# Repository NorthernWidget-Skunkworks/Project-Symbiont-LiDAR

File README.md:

# Project-Symbiont-LiDAR
Design files for a support and interface unit for the Garmin LiDAR Lite

***The symbiont.*** *Lichens, like this Reindeer Lichen found in northeastern
Minnesota, are a symbiosis between fungi and algae. Our symbiosis is between
silicon, copper, aluminum, and laser. But be it nature or machine, some
partnerships are truly mutual in their benefits. Photo by Homer Edward Price.*

The [LiDAR Lite](https://buy.garmin.com/en-US/US/p/578152/pn/010-01722-10) is a rangefinder from Garmin capable of returning distances to objects up to 40 m away. It is an effective sensor for water, snow, and ice levels, among other purposes. Extensive work to characterize the LiDAR Lite for environmental sensing of water levels has been performed by:

Paul, J. D., Buytaert, W., & Sah, N.(2020). A technical evaluation of lidar-based measurement of riverwater levels. *Water Resources Research*, *56*, e2019WR026810. https://doi.org/10.1029/2019WR026810

## Technical specifications

### Electronic Hardware

* Microcontroller (computer) core
  * ATTiny1634
  * [Firmware](Firmware) written in Arduino-compatible C++
  * 12 MHz
* Sensors
  * Externally connected: [Garmin LiDAR Lite v3 HP](https://buy.garmin.com/en-US/US/p/578152/pn/010-01722-10)
  * On board
    * MEMS accelerometer to detect board angle
    * Hall-effect sensor to for user to trigger with a magnet after providing a known angle to the accelerometer. This corrects for offset errors in the accelerometer, significantly improving its angular accuracy.
* Connections and communications protocols
  * [LiDAR Lite v3 HP](https://buy.garmin.com/en-US/US/p/578152/pn/010-01722-10)
    * 6-pin screw-terminal header
    * Switchable 5V power supply
    * I2C
  * Data logger
    * Power in and Ground
    * Digital communications
      * I2C
* Power
  * Voltage limits: 3.3 ~ 5.5V
  * Power consumption: ~0.5mA @ 4.5V, take reading every 60 seconds, then power down
  * Power conditioning: Provides an onboard, high power, step up to 5V to allow for interface to 3.3V loggers
* Fault recovery: Using intermediate system to emulate an I2C connection prevents a global lockup of the logger system
* Status LED
* Open-source licensing via CC BY-SA 4.0

### Electronic Software and Firmware

* Programmable using the Arduino IDE https://www.arduino.cc/en/main/software
* [Firmware](Firmware) available in this repository. At the time of writing, "LiDAR_InterfaceDemo" is the most up-to-date prototype firmware.
* [Software ](https://github.com/NorthernWidget-Skunkworks/Symbiont-LiDAR_Library) to use the Symbiont-LiDAR with Arduino-compatible devices
* Open-source licensing via GNU GPL 3.0

## Assembly

Assembling this sensor is possible by hand with sufficient skill and the following tools:
* Temperature-controlled soldering iron
* Hot-air rework station
* Equipment for stenciling with solder paste
* ESD-safe tweezers and workstation
* Solder wick

Most of the components on this board are coarse enough in pitch that assembly by hand is expected to be relatively straightforward. However, if you are concerned about this, there are PCB assembly workshops located in many parts of the world.
>> THOUGHT: I have basic instructions for assembly on the [Project Walrus](https://github.com/NorthernWidget-Skunkworks/Project-TPDH-Walrus) README; I will not reproduce these here just yet, as we might want to set up a separate assembly guide, mostly with good links to existing resources, since our writing something of this nature would be to reinvent the wheel.

## Firmware

### Downloading and installing the Arduino IDE

Go to https://www.arduino.cc/en/main/software. Choose the proper IDE version for your computer. For Windows, we suggest the non-app version to have more control over Arduino; this might change in the future. You will have to add custom libraries, so the web version will not work (at least, as of the time of writing). Download and install the Arduino IDE. Open it to begin the next steps.

### AVR ISP

To install firmware on the Symbiont board, you use the [2x3-pin 6-pin ICSP (also called ISP) header](https://www.digikey.com/product-detail/en/3m/929665-09-03-I/3M156313-06-ND/681796) with a special device called an "in-circuit system programmer" (or just "in-system programmer; yup, that's what the acronym stands for).

Many devices exist to upload firmware, including:
* The official [AVR ISP mkII](http://ww1.microchip.com/downloads/en/DeviceDoc/Atmel-42093-AVR-ISP-mkII_UserGuide.pdf) (no longer produced but available used)
* Using an [Arduino as an ISP](https://www.arduino.cc/en/tutorial/arduinoISP)
* The versatile [Olimex AVR-ISP-MK2](https://www.olimex.com/Products/AVR/Programmers/AVR-ISP-MK2/open-source-hardware)
* The [Adafruit USBtinyISP](https://www.adafruit.com/product/46)

### Uploading the firmware

Using this ISP, upload (as of the time of writing): [the Arduino sketch in this folder](Firmware/AdditionalFirmware/LiDAR_Accelerometer_InterfaceDemo). To do so, follow these steps:

1. Open the Arduino IDE.
2. Follow [these instructions](https://github.com/SpenceKonde/ATTinyCore/blob/master/Installation.md) to install the [ATTinyCore board definitions](https://github.com/SpenceKonde/ATTinyCore)
3. Select [ATTiny1634](https://github.com/SpenceKonde/ATTinyCore/blob/master/avr/extras/ATtiny_1634.md) **(No bootloader)**
4. Plug your ISP of choice into your computer (via a USB cable) and onto the 6-pin header. There are two ways to place it on; the header is aligned such that the ribbon cable should be facing away from the board while programming. If this fails without being able to upload, try flipping the header around. This should both power the board and provide communications.
5. Go to Tools --> Programmer and select the appropriate programmer based on what you are using.
6. Go to Tools --> Burn Bootloader. Yes, we know that you just selected "ATTiny1634 (No bootloader)", but this step sets the fuses, which configure their internal oscillator and brown-out detection.
7. Go to Sketch --> Upload Using Programmer. After several seconds, you learn whether you succeeded or failed. Hopefully it worked!

***Uploading using the in-system programmer.***

***Important note for Linux users:*** You must supply permissions to the Arduino IDE for it to be able to use the ICSP, or you will have to run it using `sudo`. The former option is better; the latter is easier in the moment.

***Note: Be sure to download and/or update drivers for your ISP.***

## Writing a program to connect to the Symbiont-LiDAR

Once it is bootloaded and connected with a LiDAR Lite sensor, you should be able to use any standard Arduino device to connect to it and read its data.

### Very simple Arduino code

This code is intended for any generic Arduino system.

```c++
// Include the Symbiont library
#include "SymbiontLiDAR.h"

// Declare variables -- just as strings
String header;
String data;

// Instantiate class
SymbiontLiDAR myLaser;

void setup(){
    // Begin Serial connection to computer at 38400 baud
    Serial.begin(38400);
    // Obtain the header just once
    header = myLaser.getHeader();
    // Print the header to the serial monitor
    Serial.println(header);
}

void loop(){
    // Take one reading every (10 + time to take reading) seconds
    // and print it to the screen
    myLaser.updateMeasurements();
    data = myLaser.getString();
    Serial.println(data);
    delay(10000); // Wait 10 seconds before the next reading, inefficiently
}
```

### Northern Widget Margay code

The [Margay data logger](github.com/NorthernWidget-Skunkworks/Project-Margay) is the lightweight and low-power open-source data-logging option from Northern Widget. It saves data to a local SD card and includes on-board status measurements and a low-drift real-time clock. We have written [a library to interface with the Margay](github.com/NorthernWidget-Skunkworks/Margay_Library), which can in turn be used to link the Margay with sensors.

```c++
// Include the Symbiont library
#include "Margay.h"
#include "SymbiontLiDAR.h"

// Declare variables -- just as strings
// Empty header to start; will include sensor labels and information
String header = "";
String data;

// Instantiate classes
SymbiontLiDAR myLaser;
Margay Logger; // Margay v2.2; UPDATE CODE TO INDICATE THIS

// I2CVals for Symbiont
uint8_t I2CVals[] = {0x50}; // DEFAULT

//Number of seconds between readings
uint32_t updateRate = 60;

void setup(){
    header = header + myLaser.getHeader();
    Logger.begin(I2CVals, sizeof(I2CVals), header);
    initialize();
}

void loop(){
    Logger.run(update, updateRate);
}

String update() {
    initialize();
    return myLaser.getString();
}

void initialize(){
    myLaser.begin();
}
```

### Northern Widget Resnik code

>> Currently nearly identical to Margay code, by design. Add telemetry with Particle Boron.

```c++
// Include the Symbiont library
#include "Resnik.h"
#include "SymbiontLiDAR.h"

// Declare variables -- just as strings
// Empty header to start; will include sensor labels and information
String header;
String data;

// Instantiate classes
SymbiontLiDAR myLaser;
Resnik Logger;

// I2CVals for Symbiont
uint8_t I2CVals[] = {0x50}; // DEFAULT

//Number of seconds between readings
uint32_t updateRate = 60;

void setup(){
    header = header + myLaser.getHeader();
    Logger.begin(I2CVals, sizeof(I2CVals), header);
    initialize();
}

void loop(){
    Logger.run(update, updateRate);
}

String update() {
    initialize();
    return myLaser.getString();
}

void initialize(){
    myLaser.begin();
}
```

## Housing and cabling

### Parts required

This is what we used for our build; you can be creative based on materials and availability.

* Main enclosure
  * Polycase box [WC-20F (clear lid)](https://www.polycase.com/wc-20f)
  * [2x \#4 screws](https://www.polycase.com/screws-mbr-100) to mount Symbiont in box
  * Cable gland ([Heyco M4365](https://www.heyco.com/Liquid_Tight_Cordgrips/product.cfm?product=Liquid-Tight-Cordgrips-Metric&section=Liquid_Tight_Cordgrips)) for cable to LiDAR Lite
  * Strain-relieved cable gland ([Heyco M4425](https://www.heyco.com/Liquid_Tight_Cordgrips/product.cfm?product=Liquid-Tight-Cordgrips-Pigtail-Metric&section=Liquid_Tight_Cordgrips)) for cable to logger
  * Desiccant packs
* LiDAR Rangefinder and attachment to enclosure
  * [LiDAR Lite sensor](https://www.sparkfun.com/products/14599)
  * [4 sealing screws](https://www.mcmaster.com/90825A144/): \#4-40 x 3/8"
  * [4 washers](https://www.mcmaster.com/90107A005) for \#4 screws
  * [4 cap nuts](https://www.mcmaster.com/99022A101) for \#4-40 screws
* Mounting plate
  * Material: Acetal (Delrin) sheet: 1/4" thick. We commmonly use [12x24" black](https://www.eplastics.com/ACTLBLK0-25012X24); the black pigment increases its UV resistance
  * Rectangular dimensions for mount: 127 x 95.25 x 6.35 mm (5.00" x 3.75" x 0.25")
  * [Design](https://easel.inventables.com/projects/VMmCoOyJyiiKTospk1NBBQ) on Easel for X-carve (see also [CNC files here](CNC)). Note the 7 mm depth to ensure that the bit cuts all the way through the Acetal; use a piece of scrap material on your cutting bed if you want to protect it.
* Mounting plate fasteners
  * 1/4"-20 hardware to attach the box to the mounting plate
    * Bolts: [1" long; hex head convenient; zinc-plated medium-grade (Grade 5) recommended for lower price with good corrosion resistance](https://www.mcmaster.com/92865A542)
    * Nuts: [Zinc-plated Grade 5](https://www.mcmaster.com/95462A029)
    * Washers: Zinc-plated [SAE](https://www.mcmaster.com/90126A029) or [USS](https://www.mcmaster.com/90108A413)
    * Lock washers: We typically use [split-lock washers](https://www.mcmaster.com/zinc-plated-steel-washers/), but [tooth-lock washers](https://www.mcmaster.com/91113A029) are good for high-vibration environments.
  * 2 U bolts: 1/4"-20, inner diameter 3/4" to 1 3/4", to attach the mounting plate to a pipe. We typically mount this sensor on 3/4" pipe or conduit, and recommend a U bolt designed to fit this ([1/4"-20, 1 1/8" inner diameter](https://www.mcmaster.com/u-bolts/u-bolts-with-mounting-plates/for-pipe-size~3-4/)). Weather/corrosion resistance is helpful, especially if you are concerned about later removing the U bolts.
* Cable to logger
  * 3 m (or less) [4-conductor AlphaWire](https://www.digikey.com/product-detail/en/alpha-wire/5004C-SL001/5004CSL001-ND/484976), stripped and tinned at both ends. Other cables will work too; this is what we have found to be highest quality and reliability. We cannot guarantee successful I<sup>2</sup>C communications over cables longer than 3 meters.

***Mounting plate perspective view in [Easel](https://easel.inventables.com/projects/VMmCoOyJyiiKTospk1NBBQ)*** *for easy integration with the X-carve series of lower cost CNC routers.*

### Assembly

Prior to assembly, ensure that you have:
* [Uploaded the firmware to the Symbiont board](#Uploading-the-firmware)
* Fabricated [the mounting plate](CNC) (see also the [Easel online CNC setup](https://easel.inventables.com/projects/VMmCoOyJyiiKTospk1NBBQ)) if desired.

1. Drill and tap 12 mm holes in the side of the box. Use a M12-1.5 tap for the threads.

2. Install the Symbiont board as shown below using two of the \#4 self-tapping screws.

3. Using the sealing screws, cap nuts, and washers, install the LiDAR Lite sensor onto the lid. By mounting the LiDAR Lite at an angle, you can fix it to the box lid in a way that still allows the box to open and close properly. The cap nuts go on the outside of the housing.

4. Thread the cables through the cable glands and attach them to the screw terminals. A 1.8 mm flat-head screwdriver can be very useful for this. Note that these cables cross the board in the above image (upper left) -- and that (unlike in the image!) you should do this *after* the board is in the box.

5. Using the switch in the box, select the desired communications protocol. For most of our uses, this is I2C.

6. Attach the cable to the data logger.

7. Test the LiDAR Lite unit.

8. When satisfied with the tests, turn off the data logger and place a protective cover over the lenses of the LiDAR Lite for safety during transport. We have [a set of "safety glasses" available for 3D printing](3Dprint). You may want to secure these in place with electrical tape.

9. Place desiccant in the box. I typically install two small desiccant packs on the side of the board above the switch and large capacitor and pack them in so they are unlikely to move; this is in order to keep the indicator LED visible.

10. Securely screw the lid onto the box to seal the LiDAR Lite + Symbiont unit.

11. Mark the corner of the box next to the Hall-effect sensor, and mark the orientations of the roll and pitch axes. The pitch axis should be positive when the long strain-relieved cable gland tilts upwards. The roll axis should be positive when, when looking at the side of the assembly such that the long strain-relieved cable gland is on the left and the laser rangefinder is pointed up, the laser rangefinder rolls towards you.

>> Add an annotated picture of Hall-Effect sensor location

12. Place the box on a measured flat surface and tap the magnet to the marked location by the Hall Effect sensor. This will appropriately zero the offsets for the sensor and increase its near-horizontal accuracy significantly. This must be done when the sensor is powered; the LED will light up during the full duration of magnetic contact. When connected to a logger, this can be done by putting the magnet in place, hitting the "RESET" button (e.g., on a Margay logger), and then holding the magnet in place with the read light on until the first reading is complete. Doing this while connected to a computer is recommended in order to see the first reading on the serial monitor and double check that the zeroing/calibration is appropriate. For a convenient magnet holder, you can use our [3D-printable magnetic wand][3Dprint], which holds a small rare-Earth magnet. This may be a generic part, though this [3/8" x 1/8" Neodymium Disk Magnet](https://www.apexmagnets.com/magnets/3-8-x-1-8-disc-neodymium-magnet) works well in our experience.

13. Use the 1/4"-20 hardware to attach the LiDAR Lite box to the mounting plate. The bolts pass through the center holes on the tabs on either side of the box, with their heads towards the box lids.

>> Note: Mounting plate holes currently too small for these; will need to be updated. Currently using #8 hardware. Figures for pitch+roll have 1/4-20 -- I probably drilled it out wider for these.

14. (Can wait for field installation) attach the unit via its mounting plate to the appropriate pipe, post, etc. This typically involves the U bolts, noted above. Curved EMT conduit can be helpful for providing a way to select the angle of the sensor. Although we use a single 45-degree bend piece of conduit in the images below, we might suggest attaching a 90-degree bend conduit first, and then a 45-degree bend as necessary to adjust the sensor away from a direct down-looking view; the sensor will attach directly to the convex side of the bend instead of bridging over airspace, which required us to use rocks as shims to reduce mounting-plate flexure. (This suggestion, however, increases torque on the mast; future field testing is needed to determine the best method.) ***Note: The LiDAR Lite unit will likely give a return only if its angle to the surface that it is measuring is steeper (i.e., more orthogonal) than 45 degrees.***

## Field installation

***Lab mock-up of field installation for LiDAR Lite.*** *The boxes at right contain [Northern Widget Margay](https://github.com/NorthernWidget-Skunkworks/Project-Margay) data loggers with a single cable gland to connect to the Symbiont box. The two posts next to them provide examples of how to connect the 3/4" EMT conduit to some fixed point in the environment, either the side of a flat(ish) wall (right) -- though the brackets aren't necessary or even always good, since we can bolt right through the pipe -- or to a flat(ish) surface using a floor flange. We drilled holes through the conduit to attach 1/4" eye bolts (1/4"-20, 1.5" long) using nuts, lock washers, and washers, to the conduit. These eye bolts then held turnbuckles to which we attached cables (lower left). The other end of the cables can be attached via sleeve or wedge anchors to rock, or to other sturdy structures. The LiDAR Lite + Symbiont is in the upper left corner, albeit attached in a way that would have it looking up... unless it were attached to the end of the 90-degree bend.*

### Mast construction

#### Supplies

* 3/4" EMT rigid conduit
  * Straight: main mast
  * 90-degree bend
  * 45-degree bend
* 3/4" Conduit screw-down connectors (to join multiple pieces of conduit)
* 3/4" Conduit-to-threaded connectors (to link smooth conduit to threaded 3/4" plumbing, needed only if you use a floor flange)
* Floor flange (1, if you want to attach to a flat surface)
* 1/4-20 x 1.5" eye bolts (3, +1 in case you bend/break one)
* 1/4" x 2+" long sleeve or wedge anchors; 4 for the floor flange or 2 for bolting into the side of a rock. Extras suggested, as these can be broken during installation.
* Turnbuckles; I suggest getting 3 that are threaded all the way down (as shown in the picture above). Get an extra in case you break one.
* 1/8" metal cable
* 1/8" cable clamps (x6, +1 in case you lose the nuts)
* 1/8" metal cable turns (x6; if you lose one, don't worry; these are nice for durability but not totally necessary)
* 3/8" x 2.5+" long sleeve or wedge anchors for the cables; these are less breakable than their 1/4" cousins, but you might still want an extra one.
* Extra 1/4"-20 hardware. I almost always end up needing this.
* Cable management (keep secure and prevent from flapping in the wind, which can cause damage)
  * Cable ties (zip ties). Ensure that these are UV-resistant; many black ones are.
  * Electrical tape
* *Optional:* 2x ~1-3/4" hose clamps if mounting a data-logger box for the [Margay](https://github.com/NorthernWidget-Skunkworks/Project-Margay) on the main mast. Longer hose clamps (or multiple 1-3/4" clamps in series) for larger logger boxes, so long as they can remain stable on the mast.

You might not need the guy wires and associated hardware if you bolt your assembly to the side of something (like a rock or wall). Some guy wires are generally encouraged.

#### Assembly

***Placing and leveling the base.***

***Installing the base using wedge anchors.***

***Installing the conduit and anchoring it with eye bolts and turnbuckles.*** *Before going out to the field, we strongly suggest you pre-drill the holes and pre-install the eye bolts.*

***Tightening the cable around the bolt in the rock using the cable clamp.***

***Aiming the LiDAR Lite unit at the river.*** *In future models, we are considering adding peep sights to the mounting bracket. [Professor Billy Armstrong](https://earth.appstate.edu/faculty-staff/dr-william-h-armstrong) in the photo.*

The quality of any zeroing with the Hall-effect sensor will be limited by the ~1-degree precision of the accelerometer that is used as an inclinometer; as an additional check, it is recommended to measure and record the orientation of the field-mounted unit by hand.

***Fully installed clifftop unit***

***Fully installed clifftop unit*** *Note data-logger box attached with cable ties, as well as the mounting-plate attachment. For the latter, we used a rock as a shim with a 45-degree piece of EMS conduit. However, it may have been better to use a 90-degree piece of conduit and a 45-degree piece of conduit together to keep us from needing this shim -- though this would have increased torque on the main mast.*

***Alternative method: installing on the side of a rock.***

***Full mast installed on the side of a rock.*** *Note the LiDAR Lite + Symbiont and the data-logger box.

## Acknowledgments

Support for this project provided by:

<br/>
<br/>
<br />This work is licensed under a <a rel="license" href="http://creativecommons.org/licenses/by-sa/4.0/">Creative Commons Attribution-ShareAlike 4.0 International License</a>.

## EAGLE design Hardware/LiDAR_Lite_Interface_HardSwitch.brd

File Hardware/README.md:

`LiDAR_Lite_Interface_HardSwitch`
- A expanded version of `LiDAR_Lite_Interface`
- Adds accelerometer 
- Uses physical switch to toggle between UART and I2C communication (as opposed to being firmware controlled in `LiDAR_Lite_Interface` and `LiDAR_Lite_Interface_CAN`
- Adds power switch to disconnect LiDAR Lite 
- Adds hall effect switch to trigger auto-level or other operation

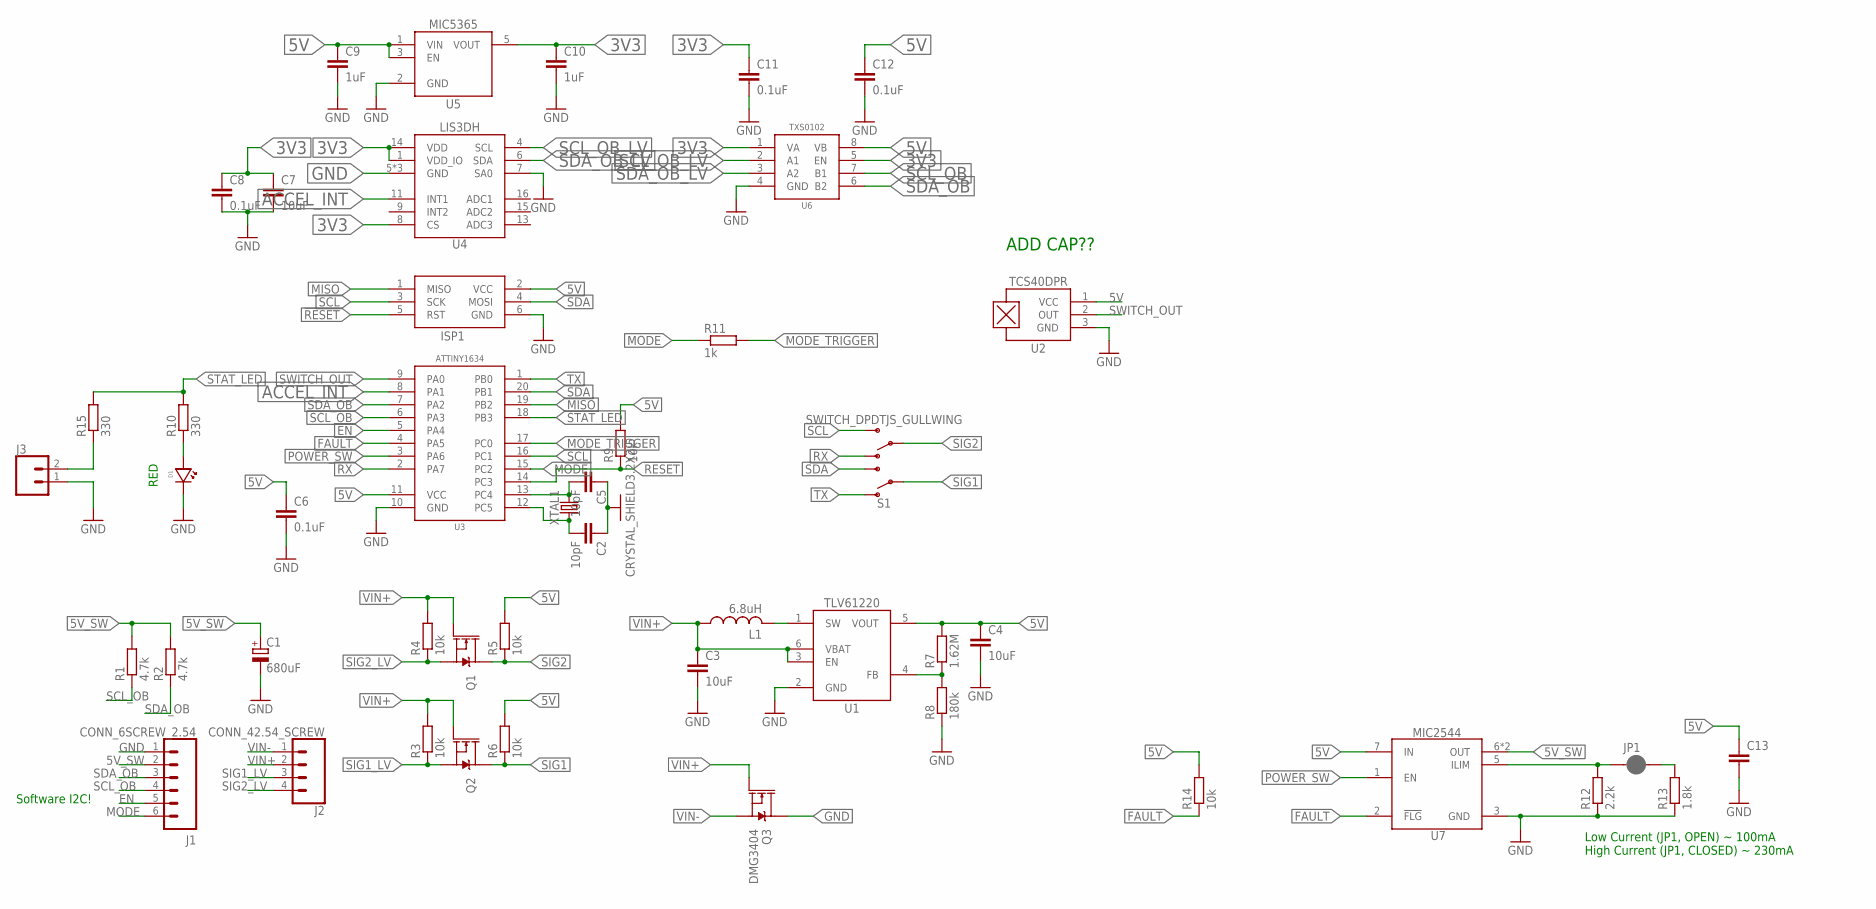
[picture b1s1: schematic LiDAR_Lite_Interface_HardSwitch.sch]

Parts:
C1: 680uF; UW-10X10_NICHICON; MPN UWT1C681MNL1GS; DIGIKEY 493-2182-1-ND
C2, C5: 10pF; C0603
C3, C4, C7: 10uF; C0805
C6, C8: 0.1uF; C0603
C9, C10: 1uF; C0603
C11, C12: 0.1uF; C0402
C13: C-EU0.1UFC0603; C0603
D1: LED0603; LED_0603; MPN 150060RS75000; DIGIKEY 732-4978-1-ND
ISP1: AVRISP-6; AVRISP
J1: CONN_6SCREW_2.54; 1X06_SCREW
J2: CONN_42.54_SCREW; 1X04_SCREW
J3: CONN_02; 1X02
JP1: JUMPER-SMT_2_NC_PASTE_SILK; SMT-JUMPER_2_NC_PASTE_SILK
L1: 6.8uH; 1008; MPN 74438323068; DIGIKEY 732-4849-1-ND
Q1, Q2: MOSFET-NCH-2N7002P; SOT23-3
Q3: DMG3404; SOT23-3
R1, R2: 4.7k; R0603
R3, R4, R5, R6, R9, R14: 10k; R0603
R7: 1.62M; R0603
R8: 180k; R0603
R10, R15: 330; R0603
R11: 1k; R0603
R12: 2.2k; R0603
R13: 1.8k; R0603
S1: SWITCH_DPDTJS_GULLWING; JS202011SCQN
U1: TLV61220DBV; DBV_R-PDSO-G6
U2: TCS40DPRSOT23; SOT23-3
U3: ATTINY1634SOIC; SO-20DW
U4: LIS3DHLGA; LGA-16
U5: MIC53653.3SC70; DCK_R-PDSO-G5
U6: TXS0102DQM; DQM_R-PX2SON-N8
U7: MIC2544MSOP; MSOP_8
XTAL1: CRYSTAL_SHIELD3.2X2.5; CRYSTAL_3.2X2.5_4-SMD; MPN ABM8G-12.000MHZ-4Y-T3; DIGIKEY 535-10901-1-ND

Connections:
3V3: C7.1, C8.1, C10.1, C11.1, U4.1 (VDD_IO), U4.8 (CS), U4.14 (VDD), U5.5 (VOUT), U6.1 (VA), U6.5 (EN)
5V: C4.1, C6.1, C9.1, C12.1, C13.1, ISP1.2 (VCC), R5.2, R6.2, R7.2, R9.2, R14.2, U1.5 (VOUT), U2.1 (VCC), U3.11 (VCC), U5.1 (VIN), U5.3 (EN), U6.8 (VB), U7.7 (IN)
5V_SW: C1.+, J1.2, R1.2, R2.2, U7.6 (OUT), U7.8 (OUT)
!RESET: ISP1.5 (RST), R9.1, U3.14 (PC3)
ACCEL_INT: U3.8 (PA1), U4.11 (INT1)
EN: J1.5, U3.5 (PA4)
FAULT: R14.1, U3.4 (PA5), U7.2 (!FLG)
GND: C1.-, C2.1, C3.2, C4.2, C5.1, C6.2, C7.2, C8.2, C9.2, C10.2, C11.2, C12.2, C13.2, D1.CATHODE, ISP1.6 (GND), J1.1, J3.1, Q3.3 (D), R8.1, R12.1, R13.1, U1.2 (GND), U2.3 (GND), U3.10 (GND), U4.5 (GND), U4.7 (SA0), U4.10 (GND), U4.12 (GND), U5.2 (GND), U6.4 (GND), U7.3 (GND), XTAL1.2 (GND), XTAL1.4 (GND)
MISO: ISP1.1 (MISO), U3.19 (PB2)
MODE: J1.6, R11.1, U3.15 (PC2)
MODE_TRIGGER: R11.2, U3.17 (PC0)
unnamed: C5.2, U3.13 (PC4), XTAL1.3 (2)
unnamed: D1.ANODE, R10.1
unnamed: C2.2, U3.12 (PC5), XTAL1.1
unnamed: J3.2, R15.1
unnamed: JP1.1, R12.2, U7.5 (ILIM)
unnamed: JP1.2, R13.2
unnamed: R7.1, R8.2, U1.4 (FB)
unnamed: L1.2, U1.1 (SW)
POWER_SW: U3.3 (PA6), U7.1 (EN)
RX: S1.6 (O2), U3.2 (PA7)
SCL: ISP1.3 (SCK), S1.4 (S2), U3.16 (PC1)
SCL_OB: J1.4, R1.1, U3.6 (PA3), U6.7 (B1)
SCL_OB_LV: U4.4 (SCL), U6.2 (A1)
SDA: ISP1.4 (MOSI), S1.3 (S1), U3.20 (PB1)
SDA_OB: J1.3, R2.1, U3.7 (PA2), U6.6 (B2)
SDA_OB_LV: U4.6 (SDA), U6.3 (A2)
SIG1: Q2.3 (D), R6.1, S1.2 (P1)
SIG1_LV: J2.3, Q2.2 (S), R3.1
SIG2: Q1.3 (D), R5.1, S1.5 (P2)
SIG2_LV: J2.4, Q1.2 (S), R4.1
STAT_LED: R10.2, R15.2, U3.18 (PB3)
SWITCH_OUT: U2.2 (OUT), U3.9 (PA0)
TX: S1.1 (O1), U3.1 (PB0)
VIN+: C3.1, J2.2, L1.1, Q1.1 (G), Q2.1 (G), Q3.1 (G), R3.2, R4.2, U1.3 (EN), U1.6 (VBAT)
VIN-: J2.1, Q3.2 (S)

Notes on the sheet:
Software I2C!
RED
ADD CAP??
Low Current (JP1, OPEN) ~ 100mA High Current (JP1, CLOSED) ~ 230mA

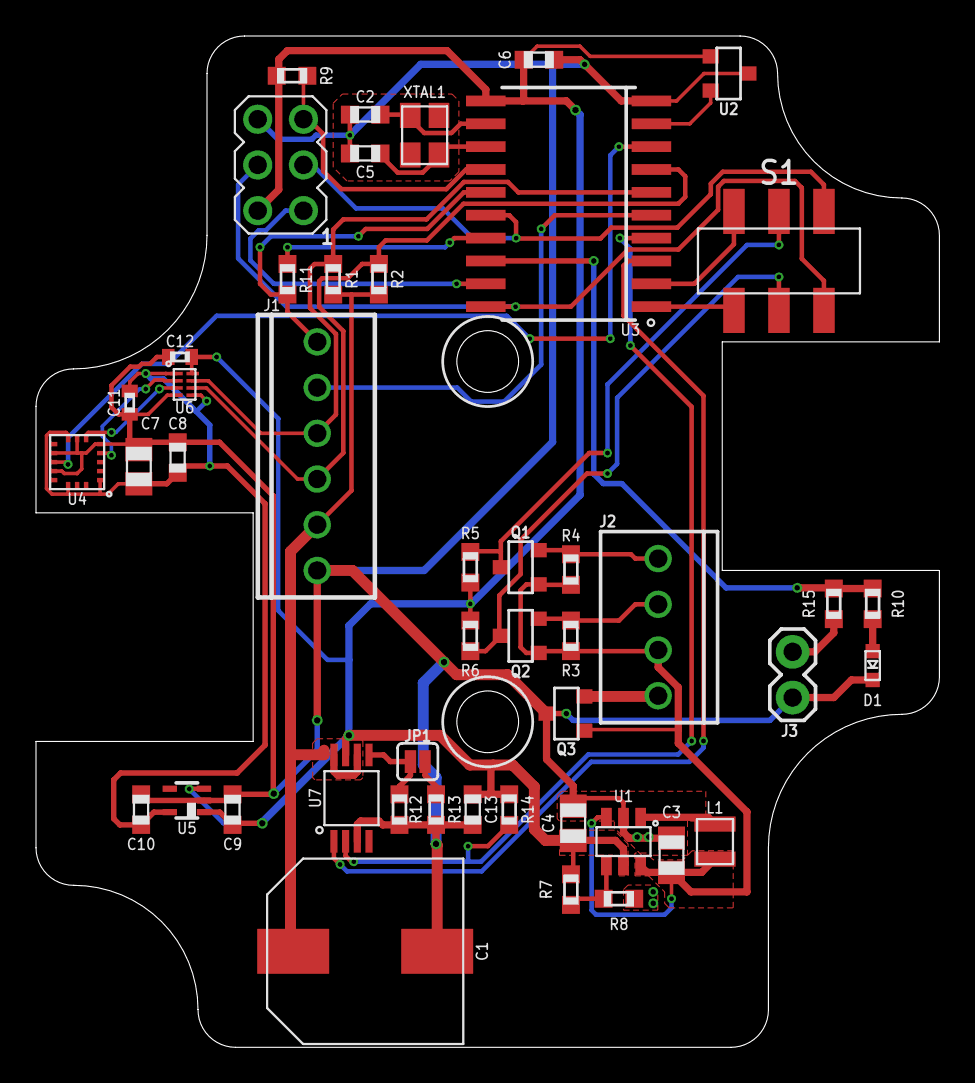
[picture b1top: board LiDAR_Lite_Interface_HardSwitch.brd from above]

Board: 2 copper layers, 50.2 x 56.2 mm, 47 parts (0 on the bottom side), 36 nets.

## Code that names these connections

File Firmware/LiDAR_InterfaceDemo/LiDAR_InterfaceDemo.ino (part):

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#define OUT_Y_ADR 0x2A
#define OUT_Z_ADR 0x2C

#define POWER_SW 2

#define ACCEL_INT 7 //Interrupt from accelerometer, active low, needs internal pullup
#define MODE_TRIGGER 13 //Trigger for pulse width mode
#define MODE_READ 11 //Read pin for pulse width mode, also INTO
#define STAT_LED 14 //Status LED
#define HALL_SWITCH 8 //Hall effect switch output 
#define ENABLE 4 //Enable pin for Lidar Lite

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  // Serial.println("begin"); //DEBUG!
  // pinMode(ADR_SEL_PIN, INPUT_PULLUP);
  // if(!digitalRead(ADR_SEL_PIN)) ADR = ADR_Alt; //If solder jumper is bridged, use alternate address //DEBUG!
  pinMode(STAT_LED, OUTPUT);
  digitalWrite(STAT_LED, HIGH);
  pinMode(POWER_SW, OUTPUT);
  // digitalWrite(POWER_SW, HIGH); //Turn on power //DEBUG!
  // delay(500); //DEBUG!
	digitalWrite(POWER_SW, LOW); //Turn off output power //FIX??
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	Wire.onStop(stopEvent);

	
	pinMode(ACCEL_INT, INPUT); //DEBUG! 
	pinMode(MODE_READ, INPUT);
	pinMode(MODE_TRIGGER, OUTPUT);
	pinMode(HALL_SWITCH, INPUT); 
	pinMode(ENABLE, OUTPUT);
	digitalWrite(ENABLE, LOW);
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
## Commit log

2019-07-10 Added Licence
2019-07-10 Added Eagle gitignore
2019-07-11 Preliminary design and layout
    Very minimal layout, first round of schematic design
2019-07-13 Updated layout, added variants
    Improved layout, potentially add button, then ready to send to fab. Added variations of layout for potential future alteration
2019-07-15 Added accel and hall effect, sent to fab
    Updated layout, added accelerometer, hall effect switch, generated gerbers and sent to fab
2019-07-26 Minor value updates, generated BoM
2019-07-26 Added ALPHA accelerometer interface demo
    Bug fixing with regard to data QA required
2019-07-30 Updates to fix accel, added LiDAR and I2C testing
    Fixed issue with accelerometer (simultaneous reads required to prevent increment issue), added file for testing of LiDAR interface and I2C offboard interface
2019-07-30 Added Hall Effect testing and Logger side interface demo
2019-08-10 Minor adjustments to firmware test
    Added light blink on startup, changed power sequence to reduce brownout risk
2019-08-13 Design updates and gerbers, final DFM required
    Added Gerbers for OSH park, naming update, pending v0.2 design
2019-08-13 Firmware updates, added hardware testing documentation
2019-08-14 Minor edits, changed external LED topology, sent v0.1 to fab
    Changed external LED to use independent resistor, generated gerbers, sent v0.1 to fab
2019-08-15 Added board shape drawing
2019-08-29 Added git lfs attributes
2019-08-29 Updated documentation with v0.1 testing
    Added test scope grabs and added to readme documentation
2019-08-29 Updated BoM for v0.1
2019-08-31 Updated firmware
    Added zeroing control, sleep, and other improvements
2019-09-05 Added I2C and serial parsing sketches
    Added sketches to serve as basis for library for device
2019-09-05 Performance updates to firmware demo
    Changed update time, removed START print due to causing problems with parsing serial output values, fixed random 0 output issue by forcing the on board I2C bus to be released after getting data from 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
    Documentation and clean up still needed
2019-09-06 Minor firmware updates
    Allow for remote mode control
2019-09-12 Added offset transmission
2019-09-12 Added roll/pitch calc, other minor
    Added roll/pitch, updated header, added I2C address test
2019-11-09 Added annotated PDF
2020-04-25 rm old Gerbers
2020-04-30 Physical hardware and mounts
2020-05-01 GNU GPL v3 for code products (software, firmware, etc.)
2020-05-04 Full instructions
2020-05-04 Mounting plate, "safety glasses", magnet level offset
2020-05-05 Correct punctuation and Polycase box
2020-05-07 Correct to "sensor"
2020-05-07 Updated readme to address comments
2020-05-24 Acetal sheet dimensions and links to eplastics
2020-05-25 @bschulz1701 advice: ISP power, mounting plate, hole+tap size
    Former-commit-id: 05432e0b7ff8a9273416ca4c78c0727f79e6abba
2020-05-25 CNC, magnet
    Former-commit-id: eb1ac7d58dff77736a761707db2b3ab5d5caf9d6
2020-05-25 git LFS
2020-05-25 Bold italic caption heading
2020-05-25 Symbiont mount render
2020-05-25 Copy "Range" variable to its own value (readability, not efficiency)
2020-05-25 Firmware: ATTinyCore
2020-05-25 ICSP header 0.1" part link
2020-05-25 Firmware section heading
2020-05-25 bootloader --> firmware
2020-05-27 U bolt dimensions for mounting plate
2020-05-27 Black acetal (UV); 1 1/8" U bolts for 3/4" pipe
2020-05-29 Naming consistency
2020-05-29 No leadless packages: can be hand soldered
2020-05-29 Basic info from @bschulz1701
2020-05-29 Most basic board: initial design
2020-05-29 Design info from @bschulz1701
2020-05-29 Partial or specialized firmware per @bschulz1701
2020-05-29 Remove "demo" moniker: this is the operational version
2020-05-29 I2CParse is most updated per #9
2020-05-31 Hardware + links
2020-05-31 Engraving/marking (xyz, magnet) now in Issues
2020-05-31 Make status LED flash patterns: now issue #13
2020-05-31 Installation hardware, supplies, and conduit
2020-05-31 Inline note to Issue #14: power consumption from lab notebook
2020-05-31 Firmware version formalized
2020-06-04 All example code compiles
2020-06-18 Acknowledge support
2020-06-18 Remove blank line between images
2020-08-07 I2C address from 0x40 to 0x50 to avoid conflicts
2020-08-07 I2C address: 0x40 --> 0x50
2020-08-08 "Bootloader" for setting fuses
2020-08-10 Input range 3.3V to 5.5V
2020-08-24 3/8" sealing screw? M10 hole/tap?
2020-09-01 M12-1.5
2020-09-03 Update sealing screws and link to 3/8"
2020-11-14 Only initialize in update step; camelCase getString
2020-11-17 rm trailing whitespace
2021-03-02 DOI badge
2021-04-08 Updated assembly instructions
    bootloading, I2C, desiccant placement
2021-04-08 Hall Effect sensor labeled
2021-04-08 Instructions to zero the orientation
2021-04-08 Describe roll and pitch axis orientations and +/-
2021-04-08 field-check orientation
2021-07-10 Angle to target more orthogonal than 45 degrees
2021-07-13 Cables >3 m not sure to work (I2C)
2021-07-14 Update link to firmware
2021-07-18 run/margay logger code example cleanup
2021-07-19 ISP driver note
2021-07-22 small spellcheck
2021-07-23 quote change
2021-08-08 note consistency changes
2022-04-24 vars/examples: header and getHeader lowercase start
2022-10-12 Side-view Symbiont with pitch +/-
2022-10-12 Side-view Symbiont with roll +/-
2022-10-12 Annotated roll and pitch directions in figures
2024-09-19 Added box mechanical designs and drawings
2024-09-19 Updated README with assembly render
2024-09-19 Added PDFs of mechanical drawings
2024-09-19 Added STEP files of milled box parts
2024-09-27 Added box printing template
2024-11-02 Added documentation and mechanical design/render

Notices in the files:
README.md:
This work is licensed under a Creative Commons Attribution-ShareAlike 4.0 International License.
parts and their libraries:
SparkFun-Jumpers: Licensing: Creative Commons ShareAlike 4.0 International - https://creativecommons.org/licenses/by-sa/4.0
